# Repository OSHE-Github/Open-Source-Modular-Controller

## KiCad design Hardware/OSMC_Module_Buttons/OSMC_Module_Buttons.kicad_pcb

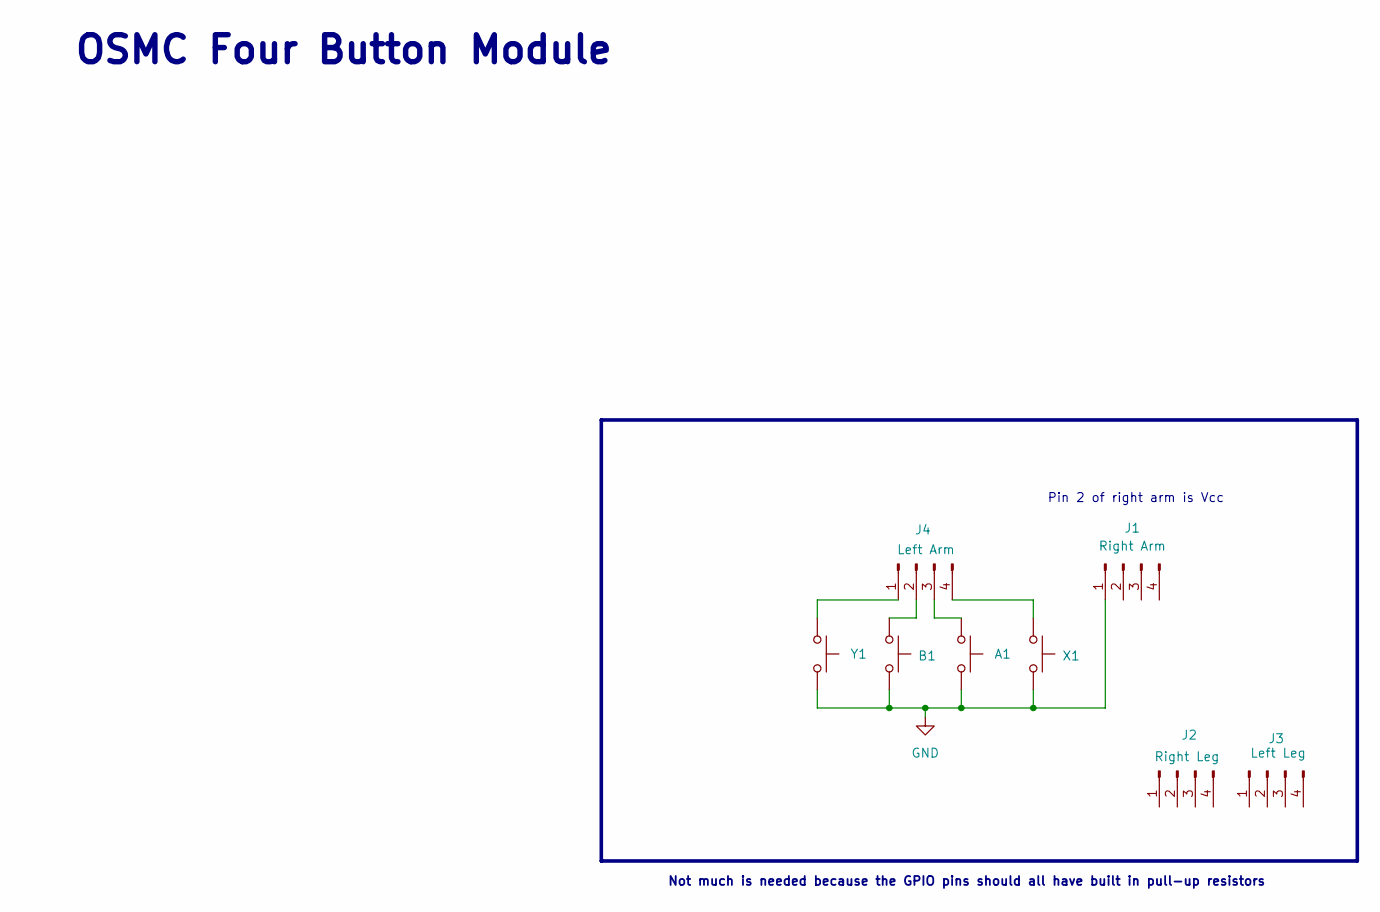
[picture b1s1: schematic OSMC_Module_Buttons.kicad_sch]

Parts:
A1: SW_TH_Tactile_Omron_B3F-100x
B1: SW_TH_Tactile_Omron_B3F-100x
J1: Right Arm; PinHeader_1x04_P2.54mm_Vertical
J2: Right Leg; PinHeader_1x04_P2.54mm_Vertical
J3: Left Leg; PinHeader_1x04_P2.54mm_Vertical
J4: Left Arm; PinHeader_1x04_P2.54mm_Vertical
X1: SW_TH_Tactile_Omron_B3F-100x
Y1: SW_TH_Tactile_Omron_B3F-100x

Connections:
GND: A1.2, B1.2, J1.1, J1.4, X1.2, Y1.2
unnamed: J4.1, Y1.1
unnamed: B1.1, J4.2
unnamed: A1.1, J4.3
unnamed: J4.4, X1.1

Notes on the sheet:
Not much is needed because the GPIO pins should all have built in pull-up resistors
Pin 2 of right arm is Vcc
OSMC Four Button Module

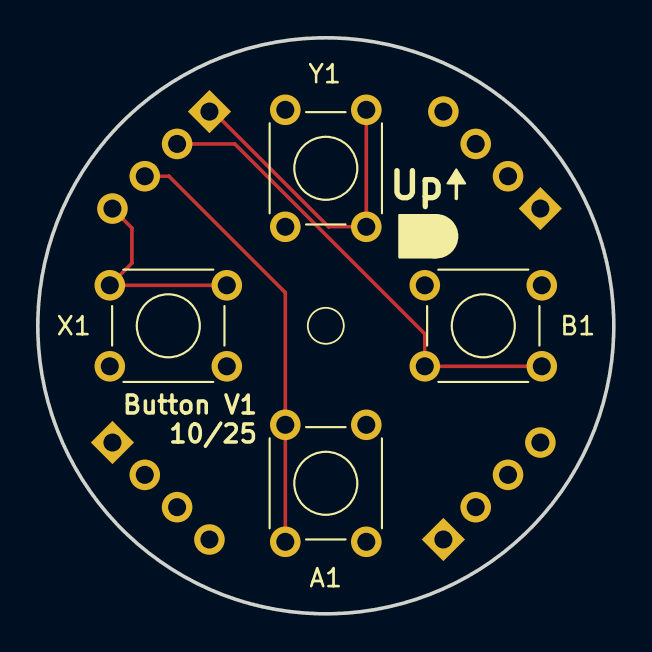
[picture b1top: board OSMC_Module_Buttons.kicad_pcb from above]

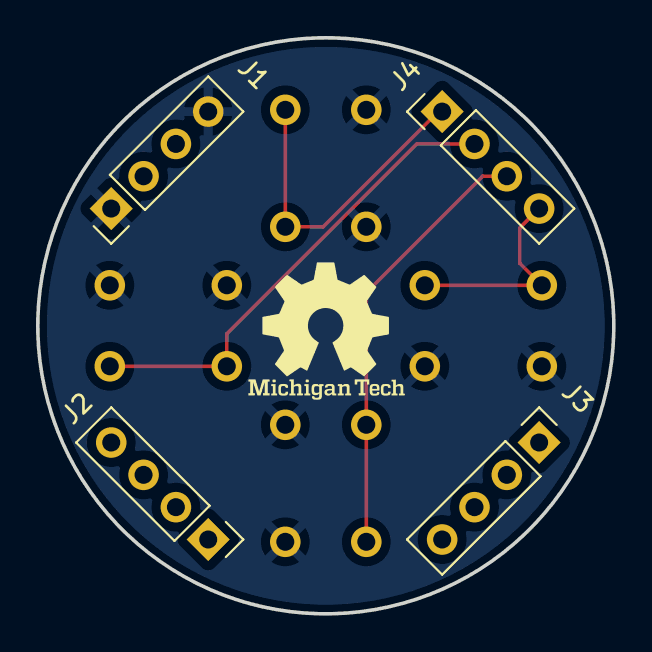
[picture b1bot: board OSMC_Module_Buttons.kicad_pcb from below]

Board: 2 copper layers, 32.0 x 32.0 mm, 8 parts (4 on the bottom side), 5 nets.

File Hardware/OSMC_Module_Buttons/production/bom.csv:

Designator,Footprint,Quantity,Value,LCSC Part #
"A1, B1, X1, Y1",SW_TH_Tactile_Omron_B3F-100x,4,~,
J1,PinHeader_1x04_P2.54mm_Vertical,1,Right Arm,
J2,PinHeader_1x04_P2.54mm_Vertical,1,Right Leg,
J3,PinHeader_1x04_P2.54mm_Vertical,1,Left Leg,
J4,PinHeader_1x04_P2.54mm_Vertical,1,Left Arm,

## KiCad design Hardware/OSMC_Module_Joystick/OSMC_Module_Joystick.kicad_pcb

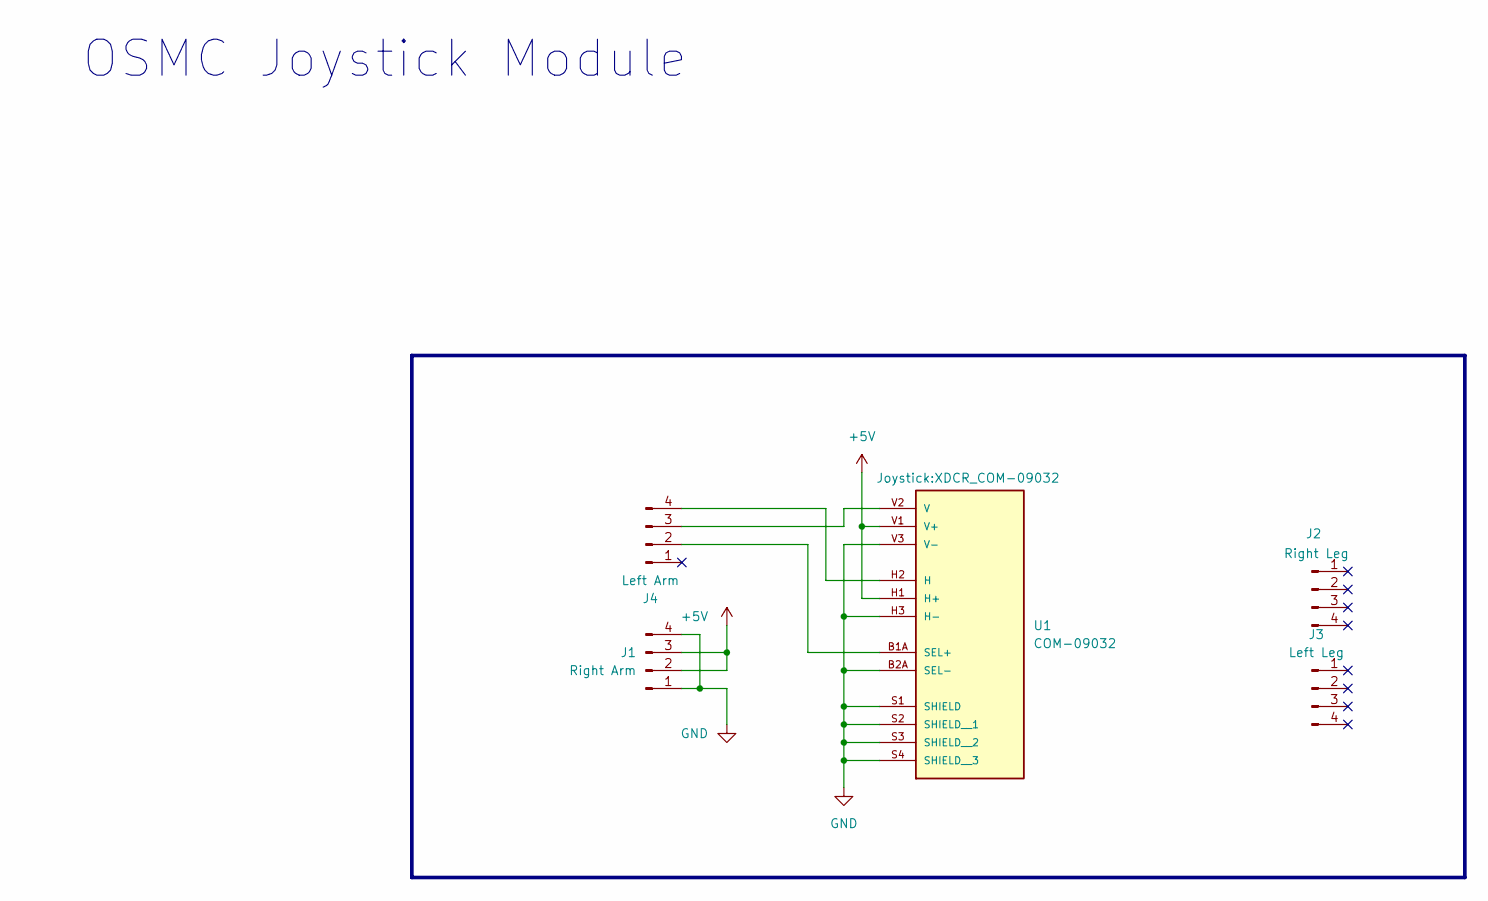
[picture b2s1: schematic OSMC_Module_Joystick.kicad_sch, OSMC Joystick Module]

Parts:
J1: Right Arm; PinHeader_1x04_P2.54mm_Vertical
J2: Right Leg; PinHeader_1x04_P2.54mm_Vertical
J3: Left Leg; PinHeader_1x04_P2.54mm_Vertical
J4: Left Arm; PinHeader_1x04_P2.54mm_Vertical
U1: COM-09032; XDCR_COM-09032; PARTREV N/A

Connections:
+5V: J1.2, J1.3, U1.H1 (H+), U1.V1 (V+)
GND: J1.1, J1.4, U1.B2A (SEL-), U1.H3 (H-), U1.S1 (SHIELD), U1.S2 (SHIELD__1), U1.S3 (SHIELD__2), U1.S4 (SHIELD__3), U1.V3 (V-)
unnamed: J4.2, U1.B1A (SEL+)
unnamed: J4.3, U1.V2 (V)
unnamed: J4.4, U1.H2 (H)

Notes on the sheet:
OSMC Joystick Module

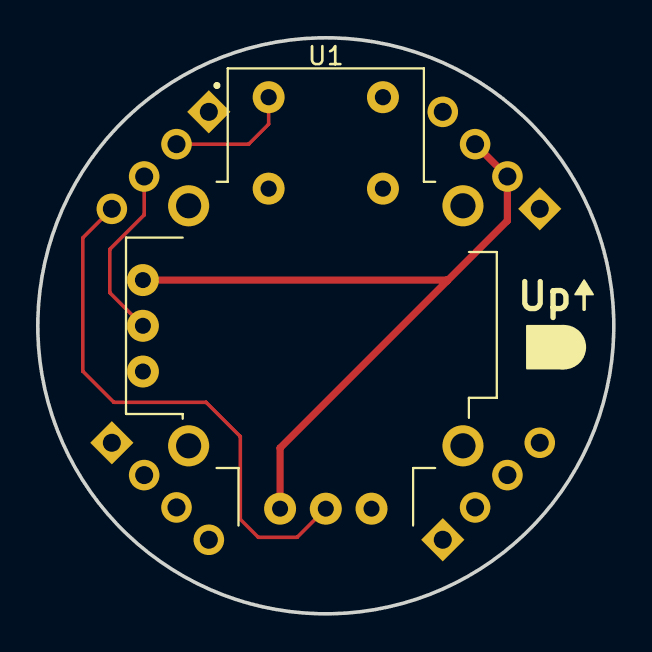
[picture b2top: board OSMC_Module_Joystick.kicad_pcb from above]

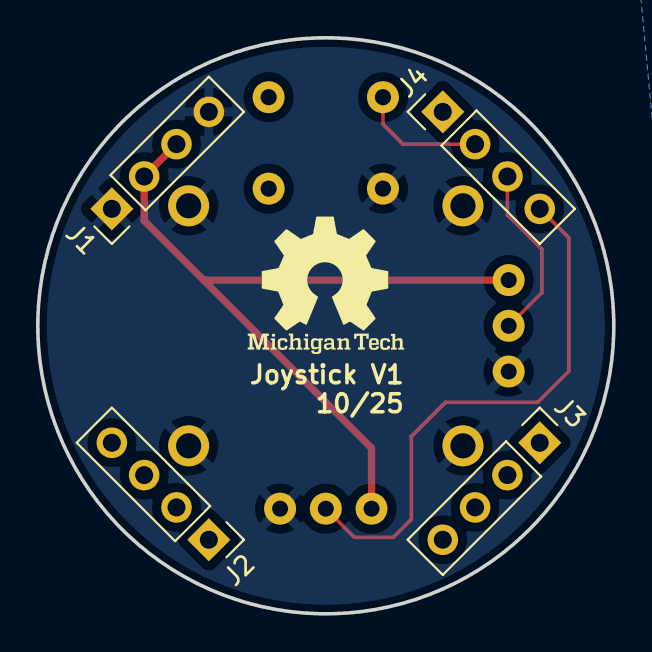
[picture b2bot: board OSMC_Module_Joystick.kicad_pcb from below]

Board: 2 copper layers, 32.0 x 32.0 mm, 5 parts (4 on the bottom side), 5 nets.

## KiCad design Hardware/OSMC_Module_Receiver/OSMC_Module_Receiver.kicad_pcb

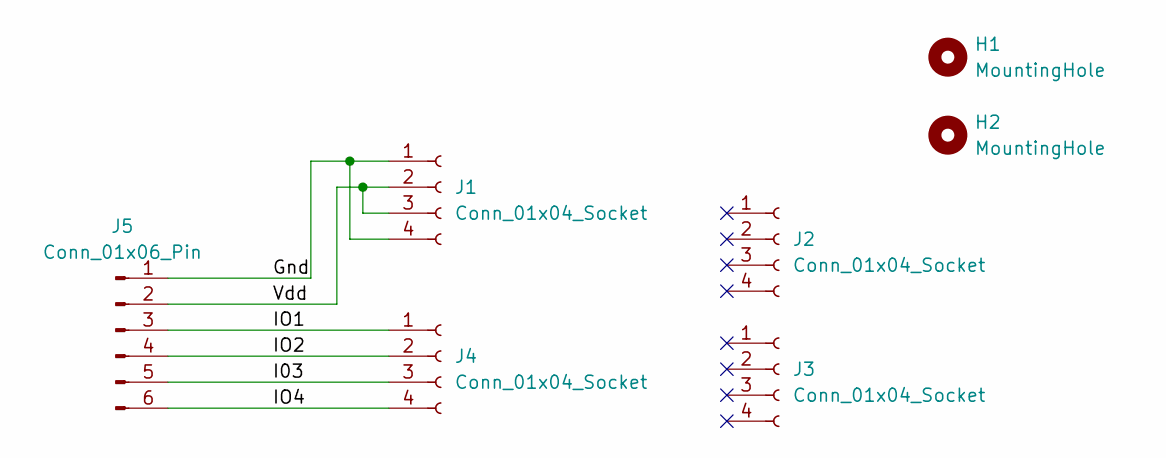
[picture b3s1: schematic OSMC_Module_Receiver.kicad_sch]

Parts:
H1, H2: MountingHole; MountingHole_2.2mm_M2
J1, J2, J3, J4: Conn_01x04_Socket; PinHeader_1x04_P2.54mm_Vertical
J5: Conn_01x06_Pin; PinHeader_1x06_P2.54mm_Vertical

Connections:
/Gnd: J1.1, J1.4, J5.1
/I03: J4.3, J5.5
/IO1: J4.1, J5.3
/IO2: J4.2, J5.4
/IO4: J4.4, J5.6
/Vdd: J1.2, J1.3, J5.2

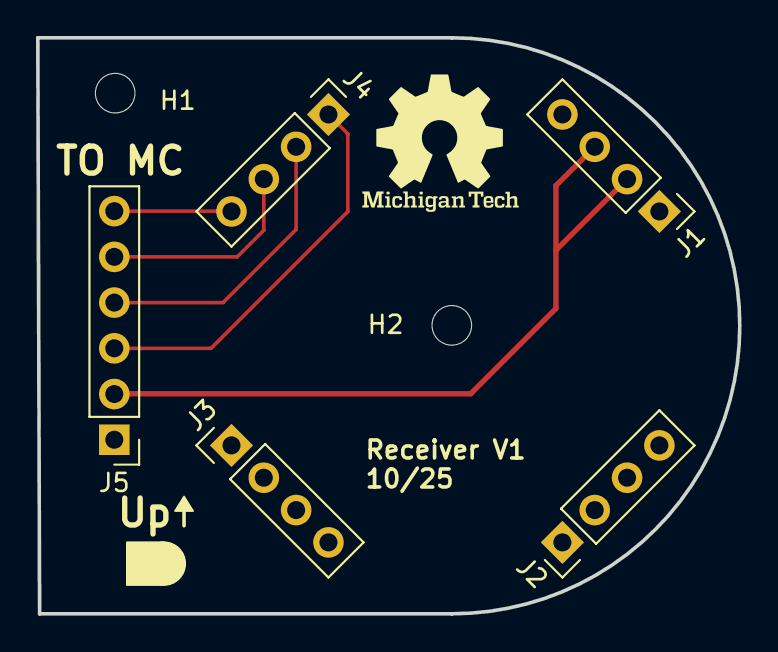
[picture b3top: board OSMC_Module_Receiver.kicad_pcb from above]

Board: 2 copper layers, 39.0 x 32.0 mm, 7 parts (0 on the bottom side), 6 nets.

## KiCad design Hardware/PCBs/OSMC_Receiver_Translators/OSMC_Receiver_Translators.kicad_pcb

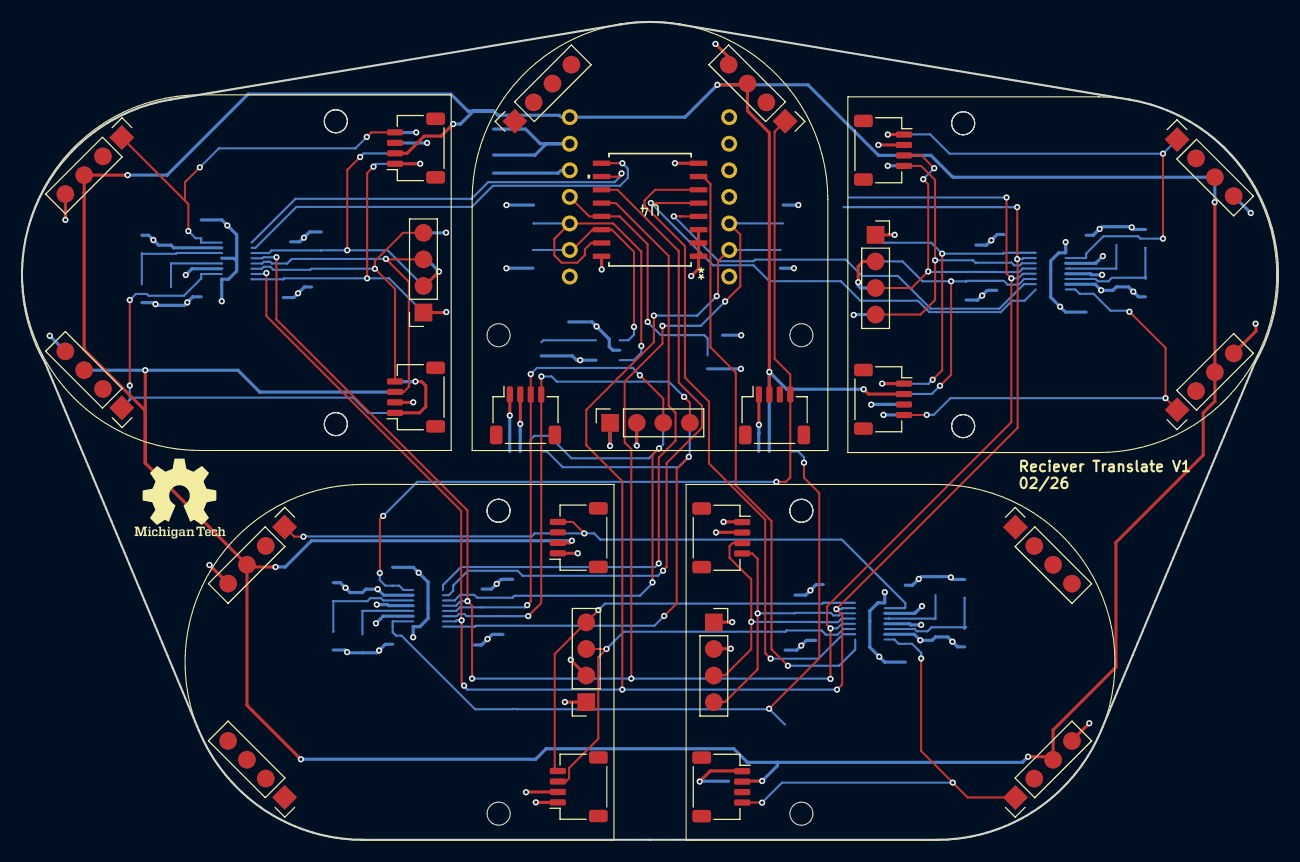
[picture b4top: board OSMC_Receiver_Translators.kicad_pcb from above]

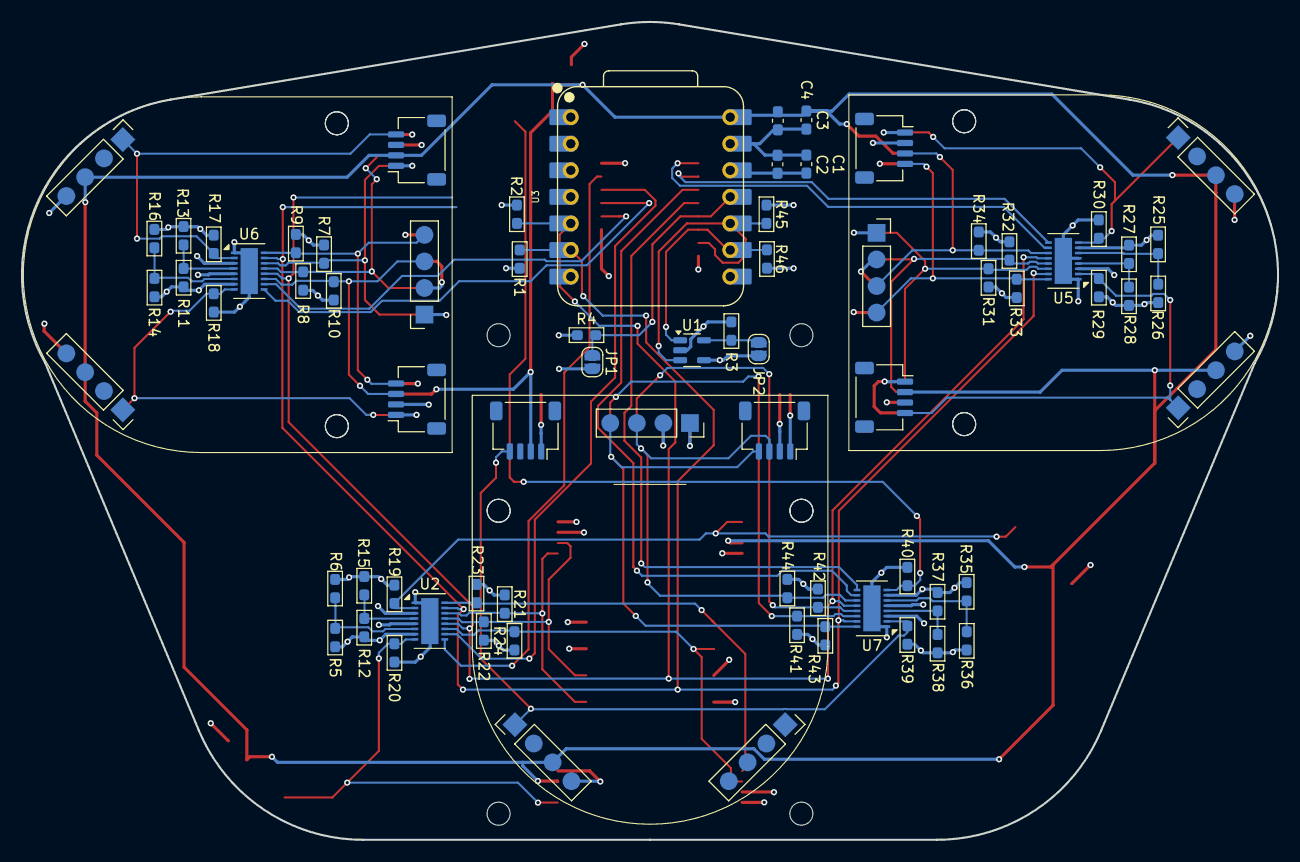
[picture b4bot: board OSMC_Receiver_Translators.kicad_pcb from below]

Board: 4 copper layers, 120.1 x 78.2 mm, 67 parts (61 on the bottom side), 49 nets.

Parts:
C1, C2: .1 u; C_0603_1608Metric_Pad1.08x0.95mm_HandSolder
C3, C4: C; C_0603_1608Metric_Pad1.08x0.95mm_HandSolder
JP1: int; SolderJumper-2_P1.3mm_Open_RoundedPad1.0x1.5mm
JP2: WP; SolderJumper-2_P1.3mm_Open_RoundedPad1.0x1.5mm
R1, R2, R7, R8, R9, R10, R17, R18, R19, R20, R21, R22, R23, R24, R29, R30, R31, R32, R33, R34, R39, R40, R41, R42, R43, R44, R45, R46: 10k; R_0603_1608Metric_Pad1.05x0.95mm_HandSolder
R3, R4: 100k; R_0603_1608Metric_Pad1.05x0.95mm_HandSolder
R5, R11: 976k; R_0603_1608Metric_Pad1.05x0.95mm_HandSolder
R6, R12: 182k; R_0603_1608Metric_Pad1.05x0.95mm_HandSolder
R13: 102k; R_0603_1608Metric_Pad1.05x0.95mm_HandSolder
R14: R; R_0603_1608Metric_Pad1.05x0.95mm_HandSolder
R15: 280k; R_0603_1608Metric_Pad1.05x0.95mm_HandSolder
R16: 0; R_0603_1608Metric_Pad1.05x0.95mm_HandSolder
R25, R27, R35, R37: 1000k; R_0603_1608Metric_Pad1.05x0.95mm_HandSolder
R26: 392k; R_0603_1608Metric_Pad1.05x0.95mm_HandSolder
R28: 523k; R_0603_1608Metric_Pad1.05x0.95mm_HandSolder
R36: 681k; R_0603_1608Metric_Pad1.05x0.95mm_HandSolder
R38: 887k; R_0603_1608Metric_Pad1.05x0.95mm_HandSolder
U1: 24AA02-OT; SOT-23-5
U2, U5, U6, U7: LTC4317; DFN-16-1EP_3x5mm_P0.5mm_EP1.66x4.4mm
U3: XIAO-ESP32-S3-DIP
U4: PCF8574DWR; DW16-L
U13, U14, U15, U16, U17, U18, U19, U20: OSMC Module Board; Module standard pin large outline

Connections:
+5V: C3.1, C4.1, U3.14 (5V), U13.10 (5V), U13.15 (5V), U14.10 (5V), U14.15 (5V), U15.10 (5V), U15.15 (5V), U16.10 (5V), U16.15 (5V), U17.10 (5V), U17.15 (5V), U18.10 (5V), U18.15 (5V), U19.10 (5V), U19.15 (5V), U20.10 (5V), U20.15 (5V)
/INT: JP1.1 (A), R4.2, U3.11 (PA6_A10_D10_MOSI), U4.13 (~INT)
/Modules/EN0: R18.2, U6.8 (ENABLE1), U13.12 (Det), U13.13 (Det)
/Modules/EN1: R17.2, U6.2 (ENABLE2), U15.12 (Det), U15.13 (Det)
/Modules/EN2: R20.2, U2.8 (ENABLE1), U16.12 (Det), U16.13 (Det)
/Modules/EN3: R19.2, U2.2 (ENABLE2), U18.12 (Det), U18.13 (Det)
/Modules/EN4: R30.2, U5.8 (ENABLE1), U17.12 (Det), U17.13 (Det)
/Modules/EN5: R29.2, U5.2 (ENABLE2), U20.12 (Det), U20.13 (Det)
/Modules/EN6: R40.2, U7.8 (ENABLE1), U14.12 (Det), U14.13 (Det)
/Modules/EN7: R39.2, U7.2 (ENABLE2), U19.12 (Det), U19.13 (Det)
/Modules/P0: U4.4 (P0), U6.10 (READY1)
/Modules/P1: U4.5 (P1), U6.9 (READY2)
/Modules/P2: U2.10 (READY1), U4.6 (P2)
/Modules/P3: U2.9 (READY2), U4.7 (P3)
/Modules/P4: U4.9 (P4), U5.10 (READY1)
/Modules/P5: U4.10 (P5), U5.9 (READY2)
/Modules/P6: U4.11 (P6), U7.10 (READY1)
/Modules/P7: U4.12 (P7), U7.9 (READY2)
/Modules/SCL0: R7.2, U6.14 (SCLOUT1), U13.4 (SCL), U13.8 (SCL)
/Modules/SCL1: R9.2, U6.16 (SCLOUT2), U15.4 (SCL), U15.8 (SCL)
/Modules/SCL2: R21.2, U2.14 (SCLOUT1), U16.4 (SCL), U16.8 (SCL)
/Modules/SCL3: R23.2, U2.16 (SCLOUT2), U18.4 (SCL), U18.8 (SCL)
/Modules/SCL4: R31.2, U5.14 (SCLOUT1), U17.4 (SCL), U17.8 (SCL)
/Modules/SCL5: R33.2, U5.16 (SCLOUT2), U20.4 (SCL), U20.8 (SCL)
/Modules/SCL6: R41.2, U7.14 (SCLOUT1), U14.4 (SCL), U14.8 (SCL)
/Modules/SCL7: R43.2, U7.16 (SCLOUT2), U19.4 (SCL), U19.8 (SCL)
/Modules/SDA0: R8.2, U6.13 (SDAOUT1), U13.3 (SDA), U13.7 (SDA)
/Modules/SDA1: R10.2, U6.11 (SDAOUT2), U15.3 (SDA), U15.7 (SDA)
/Modules/SDA2: R22.2, U2.13 (SDAOUT1), U16.3 (SDA), U16.7 (SDA)
/Modules/SDA3: R24.2, U2.11 (SDAOUT2), U18.3 (SDA), U18.7 (SDA)
/Modules/SDA4: R32.2, U5.13 (SDAOUT1), U17.3 (SDA), U17.7 (SDA)
/Modules/SDA5: R34.2, U5.11 (SDAOUT2), U20.3 (SDA), U20.7 (SDA)
/Modules/SDA6: R42.2, U7.13 (SDAOUT1), U14.3 (SDA), U14.7 (SDA)
/Modules/SDA7: R44.2, U7.11 (SDAOUT2), U19.3 (SDA), U19.7 (SDA)
/SCL: R1.2, U2.15 (SCLIN), U3.6 (PA9_A5_D5_SCL), U5.15 (SCLIN), U6.15 (SCLIN), U7.15 (SCLIN)
/SCL1: R46.2, U1.1 (SCL), U3.9 (PA7_A8_D8_SCK), U4.14 (SCL)
/SDA: R2.2, U2.12 (SDAIN), U3.5 (PA8_A4_D4_SDA), U5.12 (SDAIN), U6.12 (SDAIN), U7.12 (SDAIN)
/SDA1: R45.2, U1.3 (SDA), U3.10 (PA5_A9_D9_MISO), U4.15 (SDA)
/wp: JP2.1 (A), R3.2, U1.5 (WP)
GND: C1.2, C2.2, C3.2, C4.2, R3.1, R4.1, R6.2, R13.2, R15.2, R16.2, R17.1, R18.1, R19.1, R20.1, R26.2, R28.2, R29.1, R30.1, R36.2, R38.2, R39.1, R40.1, U1.2 (V_{SS}), U2.1 (GND), U2.3 (XORH2), U2.5 (XORH1), U2.17 (EP), U3.13 (GND), U4.1 (A0), U4.2 (A1), U4.3 (A2), U4.8 (GND), U5.1 (GND), U5.3 (XORH2), U5.5 (XORH1), U5.17 (EP), U6.1 (GND), U6.3 (XORH2), U6.5 (XORH1), U6.17 (EP), U7.1 (GND), U7.3 (XORH2), U7.5 (XORH1), U7.17 (EP), U13.1 (Gnd), U13.5 (Gnd), U13.9 (Gnd), U13.16 (GND), U14.1 (Gnd), U14.5 (Gnd), U14.9 (Gnd), U14.16 (GND), U15.1 (Gnd), U15.5 (Gnd), U15.9 (Gnd), U15.16 (GND), U16.1 (Gnd), U16.5 (Gnd), U16.9 (Gnd), U16.16 (GND), U17.1 (Gnd), U17.5 (Gnd), U17.9 (Gnd), U17.16 (GND), U18.1 (Gnd), U18.5 (Gnd), U18.9 (Gnd), U18.16 (GND), U19.1 (Gnd), U19.5 (Gnd), U19.9 (Gnd), U19.16 (GND), U20.1 (Gnd), U20.5 (Gnd), U20.9 (Gnd), U20.16 (GND)
unnamed: R5.2, R6.1, U2.6 (XORL1)
unnamed: R12.2, R15.1, U2.4 (XORL2)
unnamed: R25.2, R26.1, U5.6 (XORL1)
unnamed: R27.2, R28.1, U5.4 (XORL2)
unnamed: R14.2, R16.1, U6.6 (XORL1)
unnamed: R11.2, R13.1, U6.4 (XORL2)
unnamed: R35.2, R36.1, U7.6 (XORL1)
unnamed: R37.2, R38.1, U7.4 (XORL2)
VDD: C1.1, C2.1, JP1.2 (B), JP2.2 (B), R1.1, R2.1, R5.1, R7.1, R8.1, R9.1, R10.1, R11.1, R12.1, R14.1, R21.1, R22.1, R23.1, R24.1, R25.1, R27.1, R31.1, R32.1, R33.1, R34.1, R35.1, R37.1, R41.1, R42.1, R43.1, R44.1, R45.1, R46.1, U1.4 (V_{CC}), U2.7 (VCC), U3.12 (3V3), U4.16 (VDD), U5.7 (VCC), U6.7 (VCC), U7.7 (VCC), U13.2 (Vdd), U13.6 (Vdd), U14.2 (Vdd), U14.6 (Vdd), U15.2 (Vdd), U15.6 (Vdd), U16.2 (Vdd), U16.6 (Vdd), U17.2 (Vdd), U17.6 (Vdd), U18.2 (Vdd), U18.6 (Vdd), U19.2 (Vdd), U19.6 (Vdd), U20.2 (Vdd), U20.6 (Vdd)
